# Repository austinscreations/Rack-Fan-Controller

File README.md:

# Rack-Fan-Controller
a controller that can monitor temperature in rack enclosures and control fans

2023-10-25 files have been updated and all JLCPCB PCBa files have now been included.

fan controller is a 4 layer PCB

breakout is 2 layers

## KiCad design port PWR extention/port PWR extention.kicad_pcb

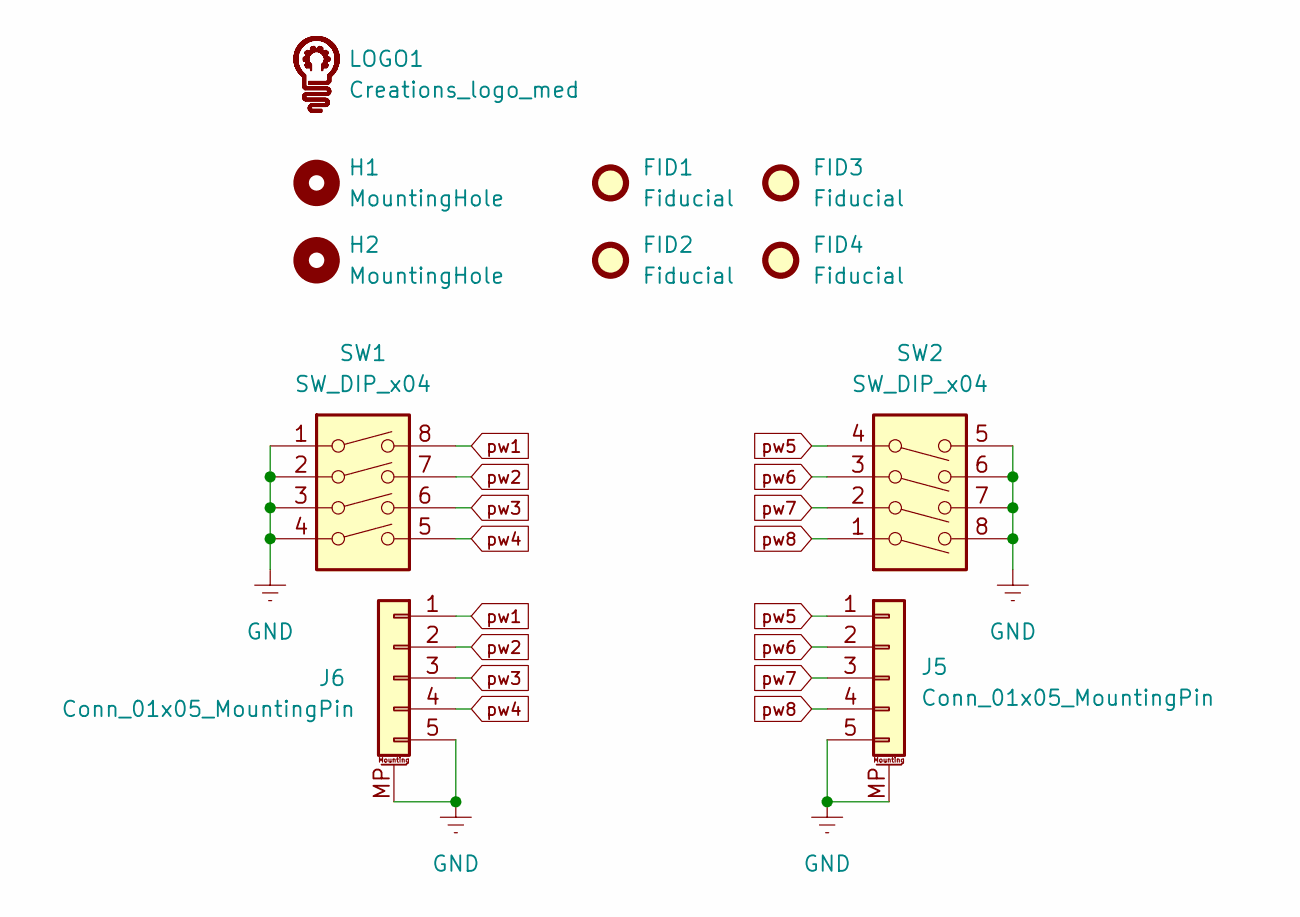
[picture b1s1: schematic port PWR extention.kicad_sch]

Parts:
FID1, FID2, FID3, FID4: Fiducial; Fiducial_1mm_Mask2mm
H1, H2: MountingHole; MountingHole_3.2mm_M3
J5, J6: Conn_01x05_MountingPin; JST_GH_SM05B-GHS-TB_1x05-1MP_P1.25mm_Horizontal; LCSC C225114
LOGO1: Creations_logo_med; Creations logo med
SW1, SW2: SW_DIP_x04; 4P_DIP; LCSC C2758183

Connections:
GNDREF: J5.5, J5.MP (MountPin), J6.5, J6.MP (MountPin), SW1.1, SW1.2, SW1.3, SW1.4, SW2.5, SW2.6, SW2.7, SW2.8
pw1: J6.1, SW1.8
pw2: J6.2, SW1.7
pw3: J6.3, SW1.6
pw4: J6.4, SW1.5
pw5: J5.1, SW2.4
pw6: J5.2, SW2.3
pw7: J5.3, SW2.2
pw8: J5.4, SW2.1

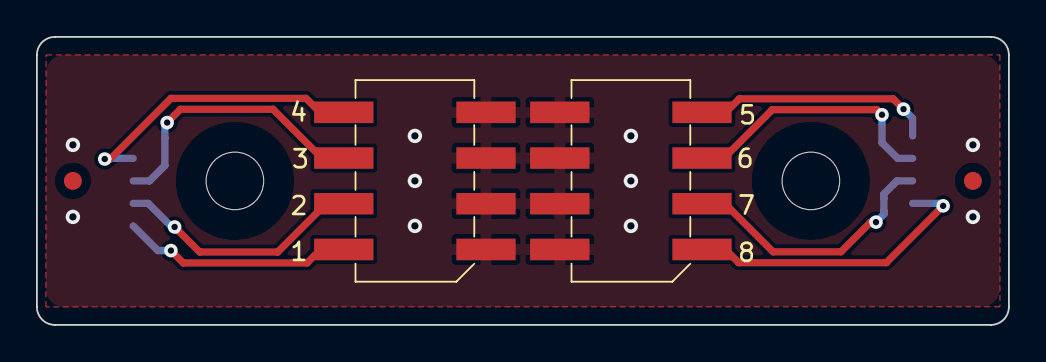
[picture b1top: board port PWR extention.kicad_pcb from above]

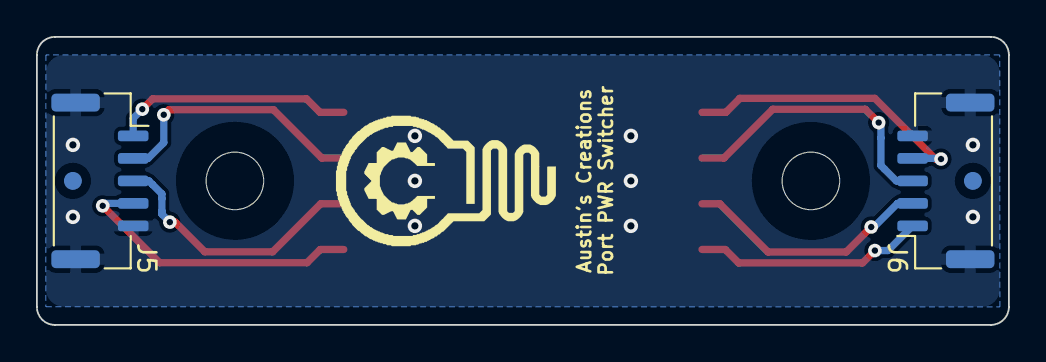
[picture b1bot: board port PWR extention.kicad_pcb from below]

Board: 2 copper layers, 54.0 x 16.0 mm, 11 parts (5 on the bottom side), 9 nets.

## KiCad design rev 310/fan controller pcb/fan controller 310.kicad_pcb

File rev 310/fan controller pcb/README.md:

fan controller has been upgraded to kicad 7 format

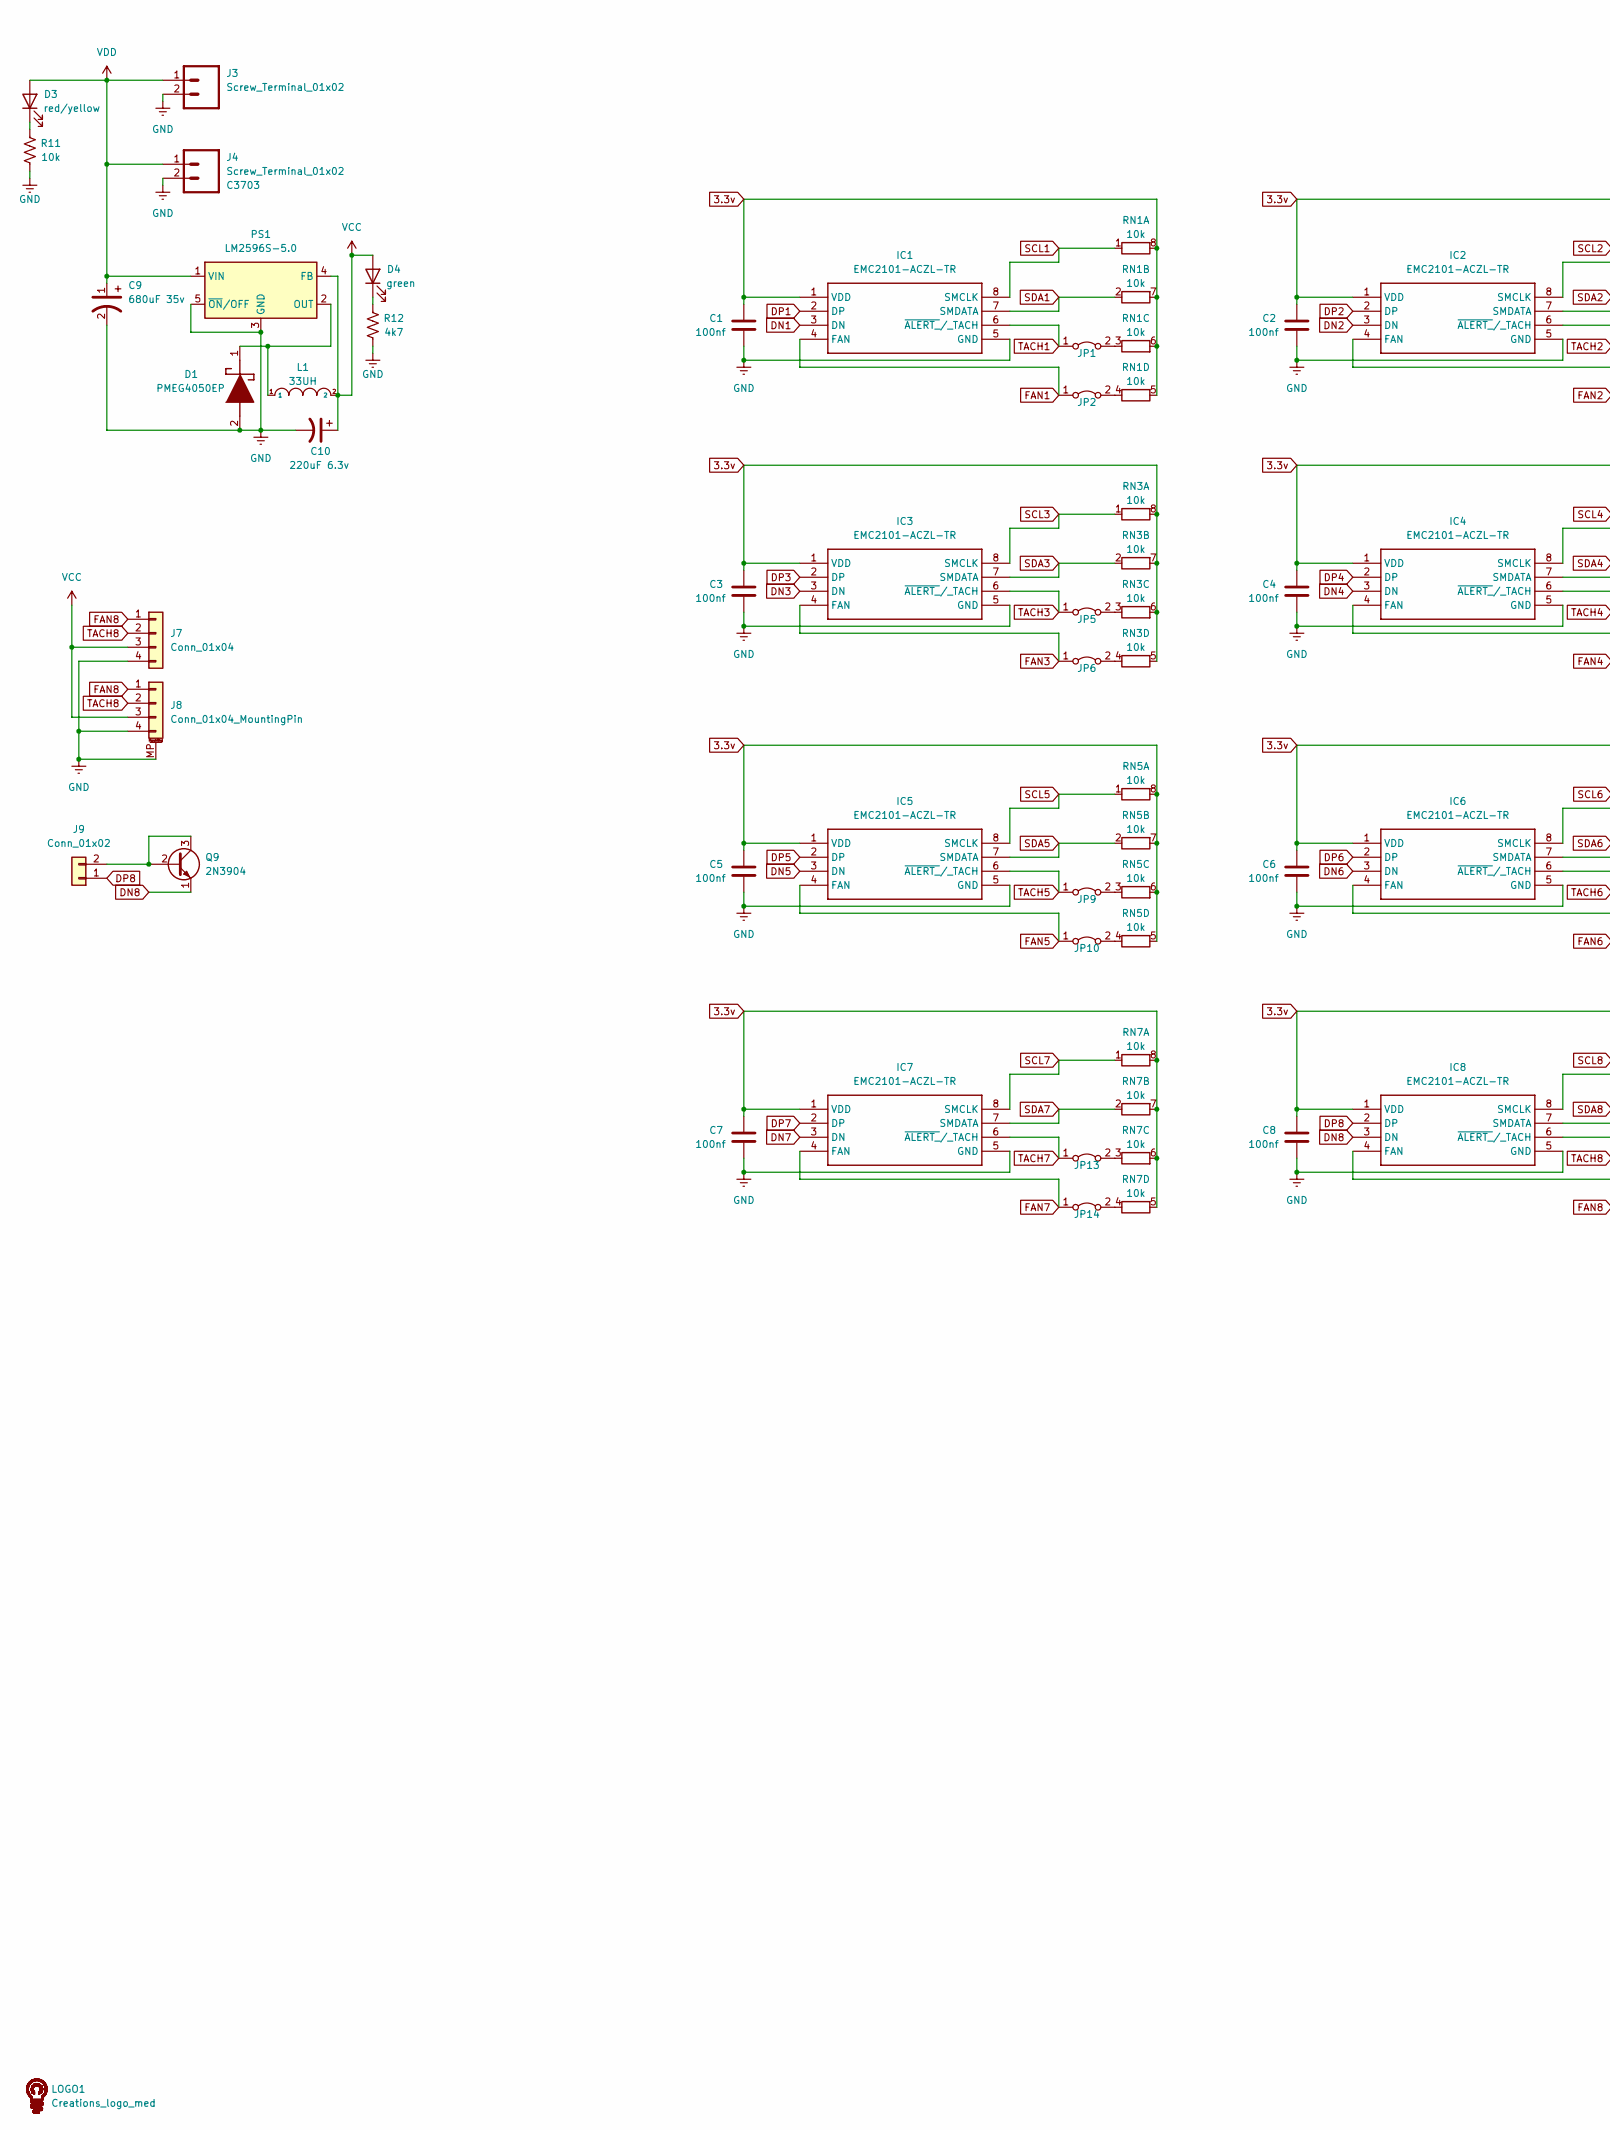
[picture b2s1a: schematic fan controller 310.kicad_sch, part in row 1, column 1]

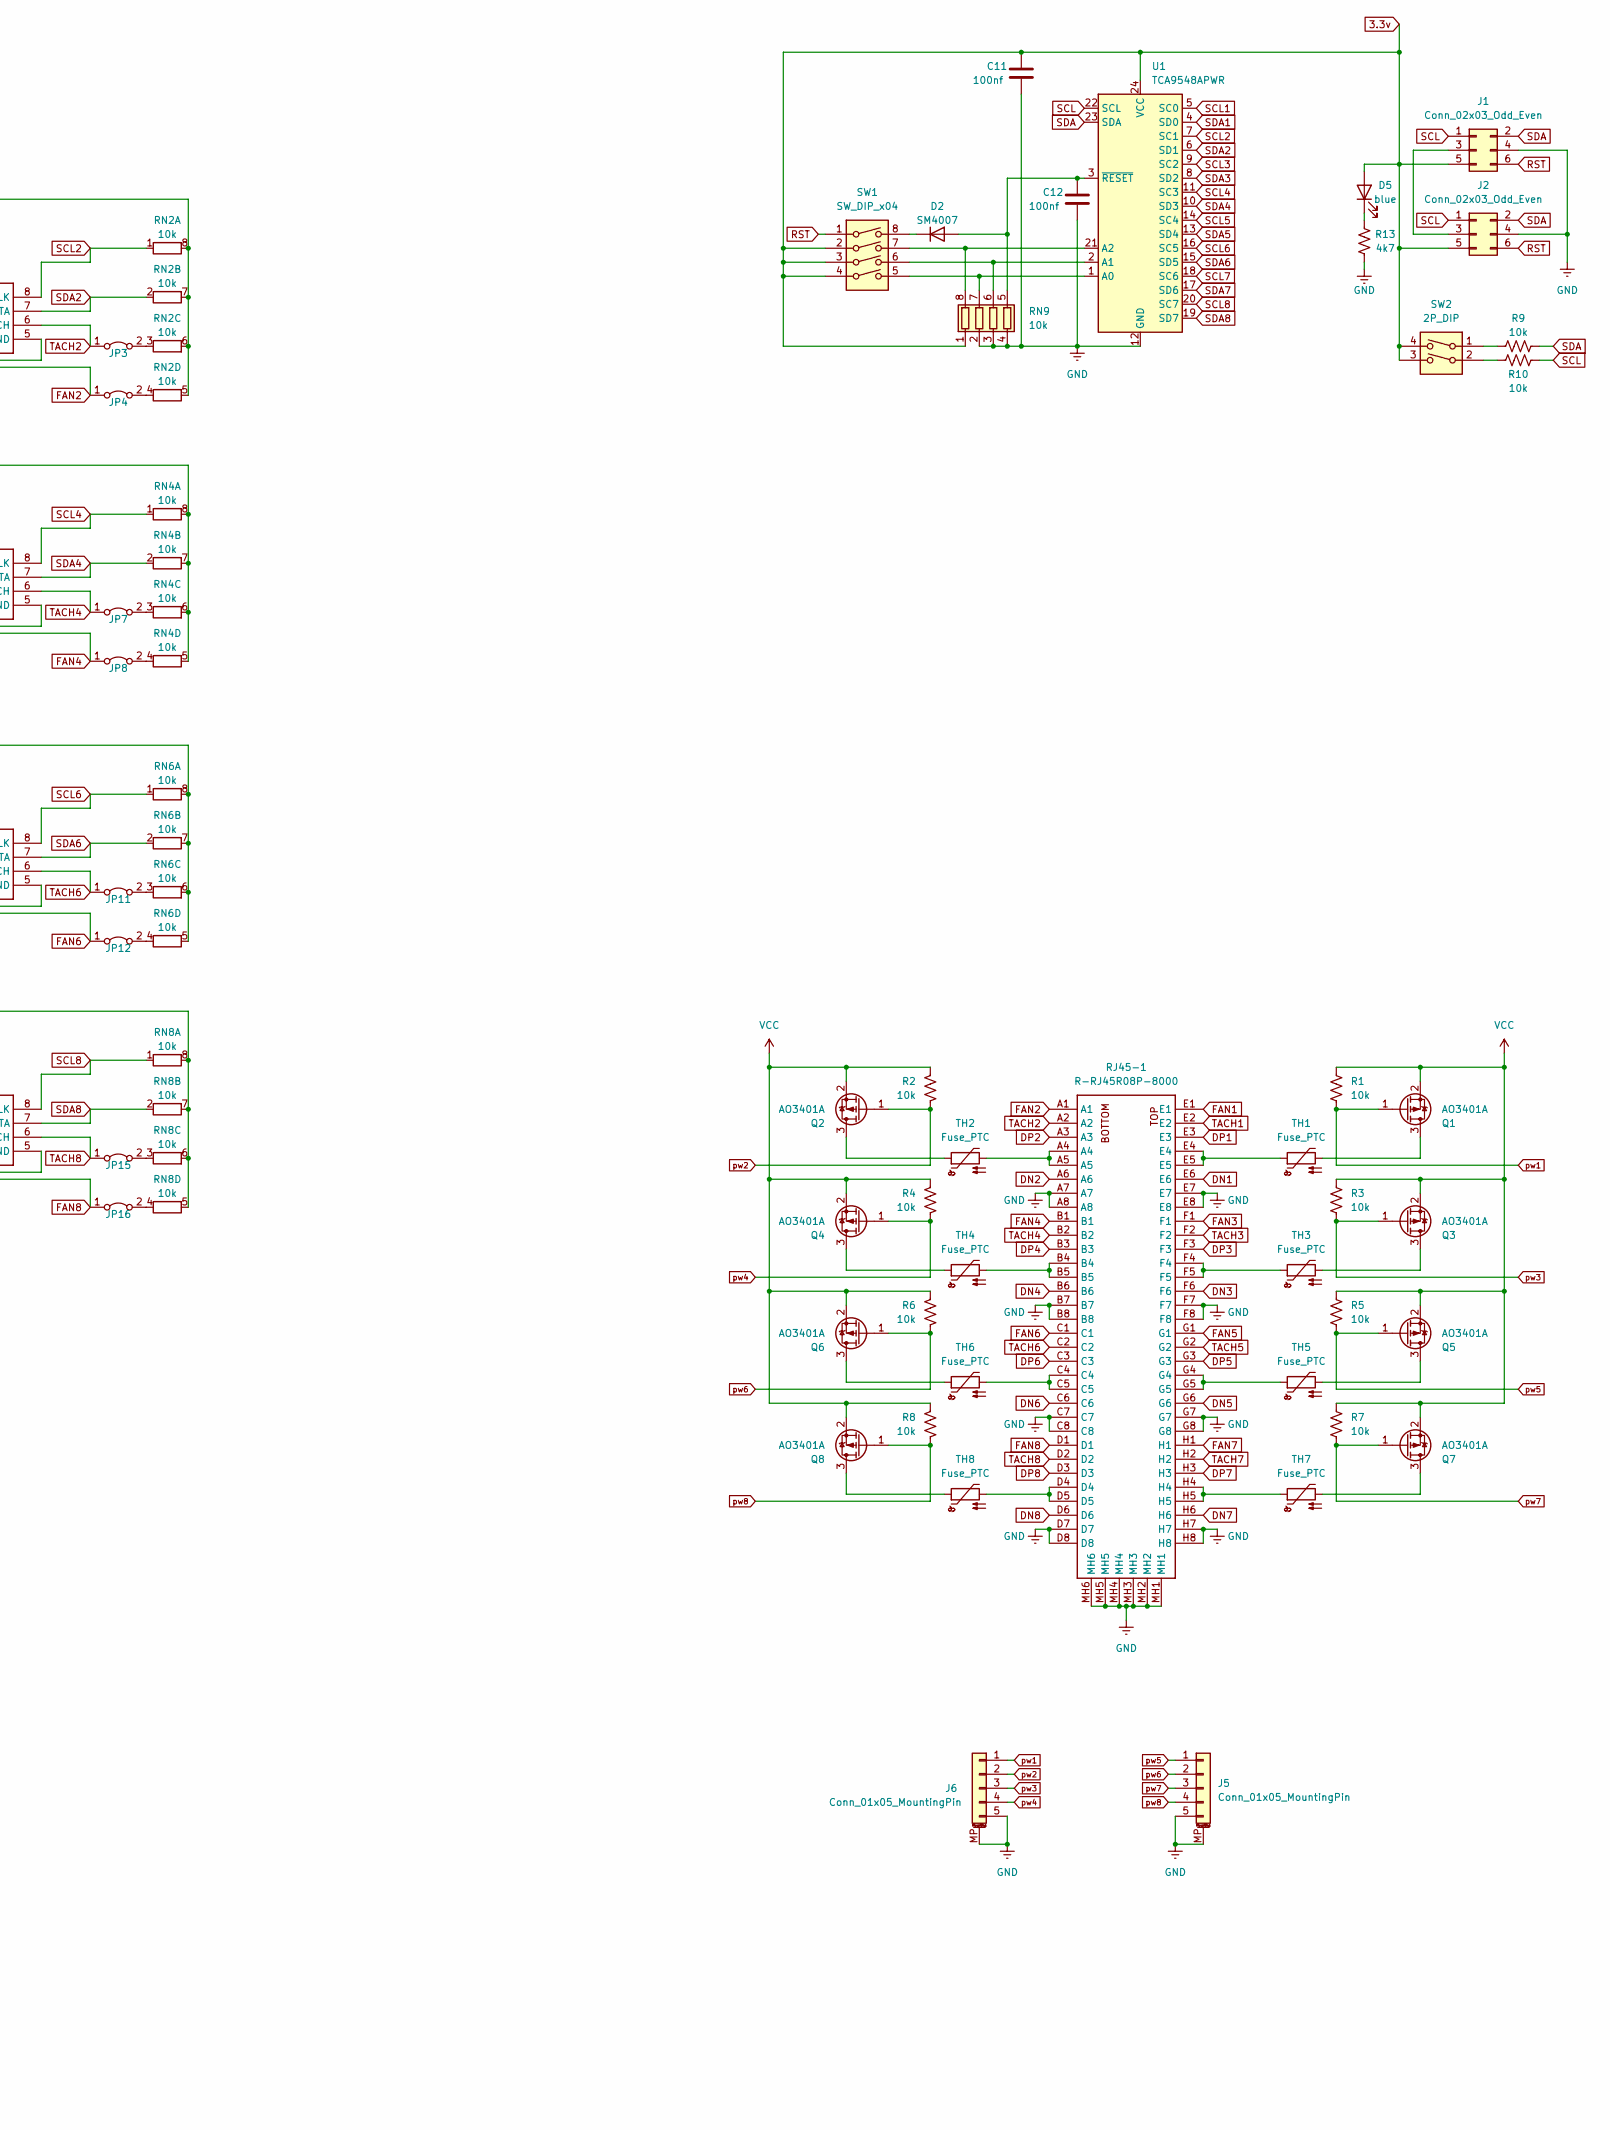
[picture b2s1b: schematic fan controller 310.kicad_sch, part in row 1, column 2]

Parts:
C1, C2, C3, C4, C5, C6, C7, C8, C11, C12: 100nf; C_0603_1608Metric; LCSC C14663
C9: 680uF 35v; large capacitor 12.5d 13.5h; LCSC C98216
C10: 220uF 6.3v; CP_Elec_8x6.2; LCSC C401613
D1: PMEG4050EP; PMEG3050EP; LCSC C96235
D2: SM4007; D_SOD-123F; LCSC C64898
D3: red/yellow; LED_0603_1608Metric; LCSC C72038
D4: green; LED_0603_1608Metric; LCSC C72043
D5: blue; LED_0603_1608Metric; LCSC C72041
IC1, IC2, IC3, IC4, IC5, IC6, IC7, IC8: EMC2101-ACZL-TR; 8-MSOP; LCSC C626967
J1, J2: Conn_02x03_Odd_Even; IDC-Header_2x03_P2.54mm_Vertical; LCSC C132438
J3, J4: Screw_Terminal_01x02; 2pinblock; LCSC C3703
J5, J6: Conn_01x05_MountingPin; JST_GH_SM05B-GHS-TB_1x05-1MP_P1.25mm_Horizontal; LCSC C225114
J7: Conn_01x04; PinHeader_1x04_P2.54mm_Vertical
J8: Conn_01x04_MountingPin; JST_GH_SM04B-GHS-TB_1x04-1MP_P1.25mm_Horizontal; LCSC C225113
J9: Conn_01x02; PinHeader_1x02_P2.54mm_Vertical; LCSC C2829889
JP1, JP2, JP3, JP4, JP5, JP6, JP7, JP8, JP9, JP10, JP11, JP12, JP13, JP14, JP15, JP16: Jumper_2_Bridged; SolderJumper-2_P1.3mm_Bridged_RoundedPad1.0x1.5mm
L1: 33UH; 12x12x8 inductor; LCSC C9400
LOGO1: Creations_logo_med; Creations logo med
PS1: LM2596S-5.0; LM2596S; LCSC C347421
Q1, Q2, Q3, Q4, Q5, Q6, Q7, Q8: AO3401A; SOT-23; LCSC C15127
Q9: 2N3904; TSOT-23; LCSC C18536
R1, R2, R3, R4, R5, R6, R7, R8, R9, R10, R11: 10k; R_0603_1608Metric; LCSC C25804
R12, R13: 4k7; R_0603_1608Metric; LCSC C23162
RJ45-1: R-RJ45R08P-8000; LCSC C386760
RN1, RN2, RN3, RN4, RN5, RN6, RN7, RN8, RN9: 10k; R_Array_Convex_4x0603; LCSC C29718
SW1: SW_DIP_x04; 4P_DIP; LCSC C2758183
SW2: 2P_DIP; LCSC C2758181
TH1, TH2, TH3, TH4, TH5, TH6, TH7, TH8: Fuse_PTC; R_0603_1608Metric; LCSC C883087
U1: TCA9548APWR; TSSOP-24_4.4x7.8mm_P0.65mm; LCSC C130026

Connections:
3.3v: C1.1, C2.1, C3.1, C4.1, C5.1, C6.1, C7.1, C8.1, C11.1, D5.2 (A), IC1.1 (VDD), IC2.1 (VDD), IC3.1 (VDD), IC4.1 (VDD), IC5.1 (VDD), IC6.1 (VDD), IC7.1 (VDD), IC8.1 (VDD), J1.5, J2.5, RN1.5 (R4.2), RN1.6 (R3.2), RN1.7 (R2.2), RN1.8 (R1.2), RN2.5 (R4.2), RN2.6 (R3.2), RN2.7 (R2.2), RN2.8 (R1.2), RN3.5 (R4.2), RN3.6 (R3.2), RN3.7 (R2.2), RN3.8 (R1.2), RN4.5 (R4.2), RN4.6 (R3.2), RN4.7 (R2.2), RN4.8 (R1.2), RN5.5 (R4.2), RN5.6 (R3.2), RN5.7 (R2.2), RN5.8 (R1.2), RN6.5 (R4.2), RN6.6 (R3.2), RN6.7 (R2.2), RN6.8 (R1.2), RN7.5 (R4.2), RN7.6 (R3.2), RN7.7 (R2.2), RN7.8 (R1.2), RN8.5 (R4.2), RN8.6 (R3.2), RN8.7 (R2.2), RN8.8 (R1.2), RN9.1 (R1.1), SW1.2, SW1.3, SW1.4, SW2.3, SW2.4, U1.24 (VCC)
DN1: IC1.3 (DN), RJ45-1.E6
DN2: IC2.3 (DN), RJ45-1.A6
DN3: IC3.3 (DN), RJ45-1.F6
DN4: IC4.3 (DN), RJ45-1.B6
DN5: IC5.3 (DN), RJ45-1.G6
DN6: IC6.3 (DN), RJ45-1.C6
DN7: IC7.3 (DN), RJ45-1.H6
DN8: IC8.3 (DN), Q9.1 (E), RJ45-1.D6
DP1: IC1.2 (DP), RJ45-1.E3
DP2: IC2.2 (DP), RJ45-1.A3
DP3: IC3.2 (DP), RJ45-1.F3
DP4: IC4.2 (DP), RJ45-1.B3
DP5: IC5.2 (DP), RJ45-1.G3
DP6: IC6.2 (DP), RJ45-1.C3
DP7: IC7.2 (DP), RJ45-1.H3
DP8: IC8.2 (DP), J9.1, RJ45-1.D3
FAN1: IC1.4 (FAN), JP2.1 (A), RJ45-1.E1
FAN2: IC2.4 (FAN), JP4.1 (A), RJ45-1.A1
FAN3: IC3.4 (FAN), JP6.1 (A), RJ45-1.F1
FAN4: IC4.4 (FAN), JP8.1 (A), RJ45-1.B1
FAN5: IC5.4 (FAN), JP10.1 (A), RJ45-1.G1
FAN6: IC6.4 (FAN), JP12.1 (A), RJ45-1.C1
FAN7: IC7.4 (FAN), JP14.1 (A), RJ45-1.H1
FAN8: IC8.4 (FAN), J7.1, J8.1, JP16.1 (A), RJ45-1.D1
GNDREF: C1.2, C2.2, C3.2, C4.2, C5.2, C6.2, C7.2, C8.2, C9.2, C10.2, C11.2, C12.2, D1.2 (A), IC1.5 (GND), IC2.5 (GND), IC3.5 (GND), IC4.5 (GND), IC5.5 (GND), IC6.5 (GND), IC7.5 (GND), IC8.5 (GND), J1.4, J2.4, J3.2, J4.2, J5.5, J5.MP (MountPin), J6.5, J6.MP (MountPin), J7.4, J8.4, J8.MP (MountPin), PS1.3 (GND), PS1.5 (~ON/OFF), R11.2, R12.2, R13.2, RJ45-1.A7, RJ45-1.A8, RJ45-1.B7, RJ45-1.B8, RJ45-1.C7, RJ45-1.C8, RJ45-1.D7, RJ45-1.D8, RJ45-1.E7, RJ45-1.E8, RJ45-1.F7, RJ45-1.F8, RJ45-1.G7, RJ45-1.G8, RJ45-1.H7, RJ45-1.H8, RJ45-1.MH1, RJ45-1.MH2, RJ45-1.MH3, RJ45-1.MH4, RJ45-1.MH5, RJ45-1.MH6, RN9.2 (R2.1), RN9.3 (R3.1), RN9.4 (R4.1), U1.12 (GND)
unnamed: D1.1 (K), L1.1, PS1.2 (OUT)
unnamed: C12.1, D2.2 (A), RN9.5 (R4.2), U1.3 (~RESET)
unnamed: D2.1 (K), SW1.8
unnamed: D3.1 (K), R11.1
unnamed: D4.1 (K), R12.1
unnamed: D5.1 (K), R13.1
unnamed: J1.3, J2.3
unnamed: J9.2, Q9.2 (B), Q9.3 (C)
unnamed: JP1.2 (B), RN1.3 (R3.1)
unnamed: JP2.2 (B), RN1.4 (R4.1)
unnamed: JP3.2 (B), RN2.3 (R3.1)
unnamed: JP4.2 (B), RN2.4 (R4.1)
unnamed: JP5.2 (B), RN3.3 (R3.1)
unnamed: JP6.2 (B), RN3.4 (R4.1)
unnamed: JP7.2 (B), RN4.3 (R3.1)
unnamed: JP8.2 (B), RN4.4 (R4.1)
unnamed: JP9.2 (B), RN5.3 (R3.1)
unnamed: JP10.2 (B), RN5.4 (R4.1)
unnamed: JP11.2 (B), RN6.3 (R3.1)
unnamed: JP12.2 (B), RN6.4 (R4.1)
unnamed: JP13.2 (B), RN7.3 (R3.1)
unnamed: JP14.2 (B), RN7.4 (R4.1)
unnamed: JP15.2 (B), RN8.3 (R3.1)
unnamed: JP16.2 (B), RN8.4 (R4.1)
unnamed: Q1.3 (D), TH1.2
unnamed: Q2.3 (D), TH2.1
unnamed: Q3.3 (D), TH3.2
unnamed: Q4.3 (D), TH4.1
unnamed: Q5.3 (D), TH5.2
unnamed: Q6.3 (D), TH6.1
unnamed: Q7.3 (D), TH7.2
unnamed: Q8.3 (D), TH8.1
unnamed: R9.1, SW2.1
unnamed: R10.1, SW2.2
unnamed: RJ45-1.A4, RJ45-1.A5, TH2.2
unnamed: RJ45-1.B4, RJ45-1.B5, TH4.2
unnamed: RJ45-1.C4, RJ45-1.C5, TH6.2
unnamed: RJ45-1.D4, RJ45-1.D5, TH8.2
unnamed: RJ45-1.E4, RJ45-1.E5, TH1.1
unnamed: RJ45-1.F4, RJ45-1.F5, TH3.1
unnamed: RJ45-1.G4, RJ45-1.G5, TH5.1
unnamed: RJ45-1.H4, RJ45-1.H5, TH7.1
unnamed: RN9.8 (R1.2), SW1.7, U1.21 (A2)
unnamed: RN9.7 (R2.2), SW1.5, U1.1 (A0)
unnamed: RN9.6 (R3.2), SW1.6, U1.2 (A1)
RST: J1.6, J2.6, SW1.1
SCL: J1.1, J2.1, R10.2, U1.22 (SCL)
SCL1: IC1.8 (SMCLK), RN1.1 (R1.1), U1.5 (SC0)
SCL2: IC2.8 (SMCLK), RN2.1 (R1.1), U1.7 (SC1)
SCL3: IC3.8 (SMCLK), RN3.1 (R1.1), U1.9 (SC2)
SCL4: IC4.8 (SMCLK), RN4.1 (R1.1), U1.11 (SC3)
SCL5: IC5.8 (SMCLK), RN5.1 (R1.1), U1.14 (SC4)
SCL6: IC6.8 (SMCLK), RN6.1 (R1.1), U1.16 (SC5)
SCL7: IC7.8 (SMCLK), RN7.1 (R1.1), U1.18 (SC6)
SCL8: IC8.8 (SMCLK), RN8.1 (R1.1), U1.20 (SC7)
SDA: J1.2, J2.2, R9.2, U1.23 (SDA)
SDA1: IC1.7 (SMDATA), RN1.2 (R2.1), U1.4 (SD0)
SDA2: IC2.7 (SMDATA), RN2.2 (R2.1), U1.6 (SD1)
SDA3: IC3.7 (SMDATA), RN3.2 (R2.1), U1.8 (SD2)
SDA4: IC4.7 (SMDATA), RN4.2 (R2.1), U1.10 (SD3)
SDA5: IC5.7 (SMDATA), RN5.2 (R2.1), U1.13 (SD4)
SDA6: IC6.7 (SMDATA), RN6.2 (R2.1), U1.15 (SD5)
SDA7: IC7.7 (SMDATA), RN7.2 (R2.1), U1.17 (SD6)
SDA8: IC8.7 (SMDATA), RN8.2 (R2.1), U1.19 (SD7)
TACH1: IC1.6 (~ALERT_/_TACH), JP1.1 (A), RJ45-1.E2
TACH2: IC2.6 (~ALERT_/_TACH), JP3.1 (A), RJ45-1.A2
TACH3: IC3.6 (~ALERT_/_TACH), JP5.1 (A), RJ45-1.F2
TACH4: IC4.6 (~ALERT_/_TACH), JP7.1 (A), RJ45-1.B2
TACH5: IC5.6 (~ALERT_/_TACH), JP9.1 (A), RJ45-1.G2
TACH6: IC6.6 (~ALERT_/_TACH), JP11.1 (A), RJ45-1.C2
TACH7: IC7.6 (~ALERT_/_TACH), JP13.1 (A), RJ45-1.H2
TACH8: IC8.6 (~ALERT_/_TACH), J7.2, J8.2, JP15.1 (A), RJ45-1.D2
VCC: C10.1, D4.2 (A), J7.3, J8.3, L1.2, PS1.4 (FB), Q1.2 (S), Q2.2 (S), Q3.2 (S), Q4.2 (S), Q5.2 (S), Q6.2 (S), Q7.2 (S), Q8.2 (S), R1.1, R2.2, R3.1, R4.2, R5.1, R6.2, R7.1, R8.2
VDD: C9.1, D3.2 (A), J3.1, J4.1, PS1.1 (VIN)
pw1: J6.1, Q1.1 (G), R1.2
pw2: J6.2, Q2.1 (G), R2.1
pw3: J6.3, Q3.1 (G), R3.2
pw4: J6.4, Q4.1 (G), R4.1
pw5: J5.1, Q5.1 (G), R5.2
pw6: J5.2, Q6.1 (G), R6.1
pw7: J5.3, Q7.1 (G), R7.2
pw8: J5.4, Q8.1 (G), R8.1

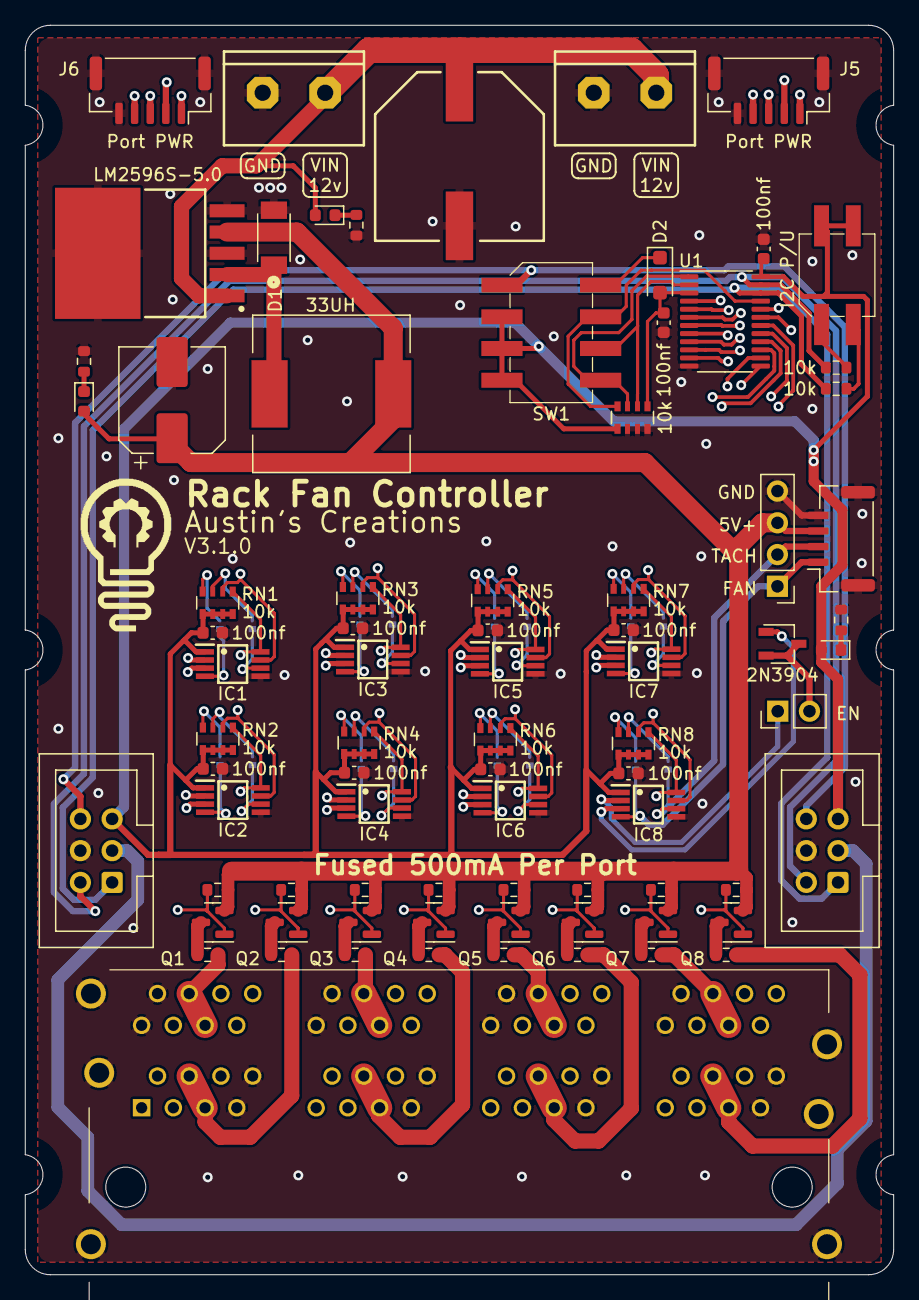
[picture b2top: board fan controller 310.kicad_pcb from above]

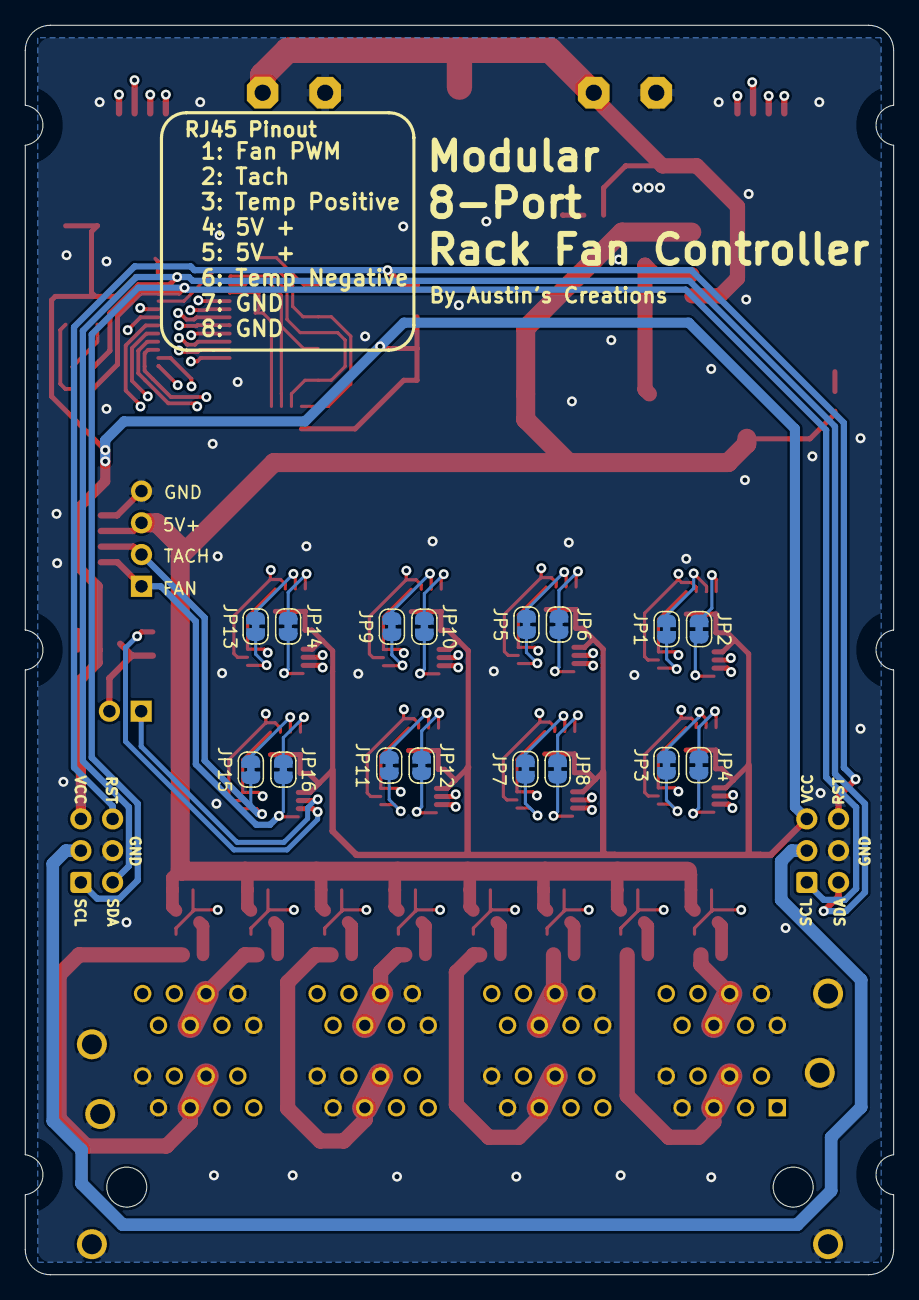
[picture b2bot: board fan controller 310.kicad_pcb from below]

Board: 4 copper layers, 69.5 x 100.0 mm, 96 parts (16 on the bottom side), 108 nets.

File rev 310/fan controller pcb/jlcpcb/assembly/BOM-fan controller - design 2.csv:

Comment,Designator,Footprint,LCSC
TCA9548APWR,U1,TSSOP-24_4.4x7.8mm_P0.65mm,C130026
Conn_02x03_Odd_Even,"J1,J2",IDC-Header_2x03_P2.54mm_Vertical,C132438
100nf,"C1,C11,C12,C2,C3,C4,C5,C6,C7,C8",C_0603_1608Metric,C14663
AO3401A,"Q1,Q2,Q3,Q4,Q5,Q6,Q7,Q8",SOT-23,C15127
2N3904,Q9,TSOT-23,C18536
Conn_01x04_MountingPin,J8,JST_GH_SM04B-GHS-TB_1x04-1MP_P1.25mm_Horizontal,C225113
Conn_01x05_MountingPin,"J5,J6",JST_GH_SM05B-GHS-TB_1x05-1MP_P1.25mm_Horizontal,C225114
4k7,"R12,R13",R_0603_1608Metric,C23162
10k,"R1,R10,R11,R2,R3,R4,R5,R6,R7,R8,R9",R_0603_1608Metric,C25804
2P_DIP,SW2,2P_DIP,C2758181
SW_DIP_x04,SW1,4P_DIP,C2758183
Conn_01x02,J9,PinHeader_1x02_P2.54mm_Vertical,C2829889
10k,"RN1,RN2,RN3,RN4,RN5,RN6,RN7,RN8,RN9",R_Array_Convex_4x0603,C29718
LM2596S-5.0,PS1,LM2596S,C347421
Screw_Terminal_01x02,"J3,J4",2pinblock,C3703
R-RJ45R08P-8000,RJ45-1,R-RJ45R08P-8000,C386760
220uF 6.3v,C10,CP_Elec_8x6.2,C401613
EMC2101-ACZL-TR,"IC1,IC2,IC3,IC4,IC5,IC6,IC7,IC8",8-MSOP,C626967
SM4007,D2,D_SOD-123F,C64898
red/yellow,D3,LED_0603_1608Metric,C72038
blue,D5,LED_0603_1608Metric,C72041
green,D4,LED_0603_1608Metric,C72043
Fuse_PTC,"TH1,TH2,TH3,TH4,TH5,TH6,TH7,TH8",R_0603_1608Metric,C883087
33UH,L1,12x12x8 inductor,C9400
PMEG4050EP,D1,PMEG3050EP,C96235
680uF 35v,C9,large capacitor 12.5d 13.5h,C98216
Conn_01x04,J7,PinHeader_1x04_P2.54mm_Vertical,

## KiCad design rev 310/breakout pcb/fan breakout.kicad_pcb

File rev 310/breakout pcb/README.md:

fan breakout has been upgraded to kicad 7 format

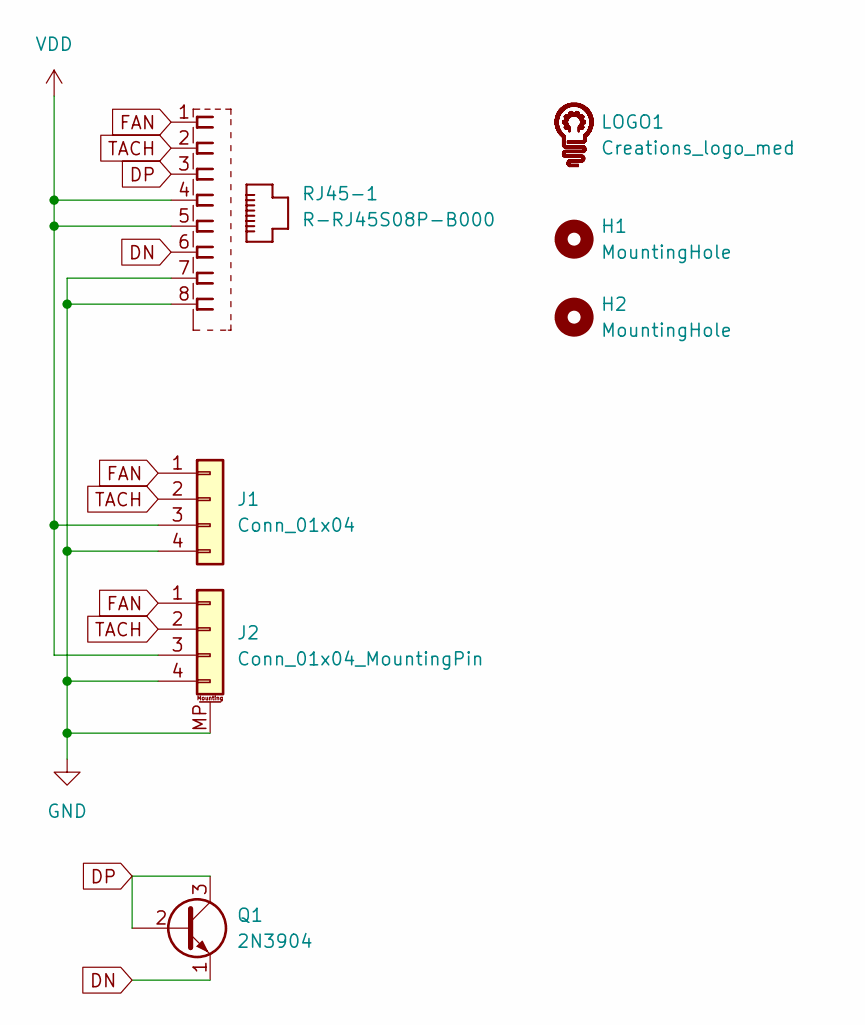
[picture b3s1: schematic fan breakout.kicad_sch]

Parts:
H1, H2: MountingHole; MountingHole_3.2mm_M3
J1: Conn_01x04; PinHeader_1x04_P2.54mm_Vertical
J2: Conn_01x04_MountingPin; JST_GH_SM04B-GHS-TB_1x04-1MP_P1.25mm_Horizontal; LCSC C225113
LOGO1: Creations_logo_med; Creations logo med
Q1: 2N3904; TSOT-23; LCSC C18536
RJ45-1: R-RJ45S08P-B000; LCSC C386763

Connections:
DN: Q1.1 (E), RJ45-1.6
DP: Q1.2 (B), Q1.3 (C), RJ45-1.3
FAN: J1.1, J2.1, RJ45-1.1
GND: J1.4, J2.4, J2.MP (MountPin), RJ45-1.7, RJ45-1.8
TACH: J1.2, J2.2, RJ45-1.2
VDD: J1.3, J2.3, RJ45-1.4, RJ45-1.5

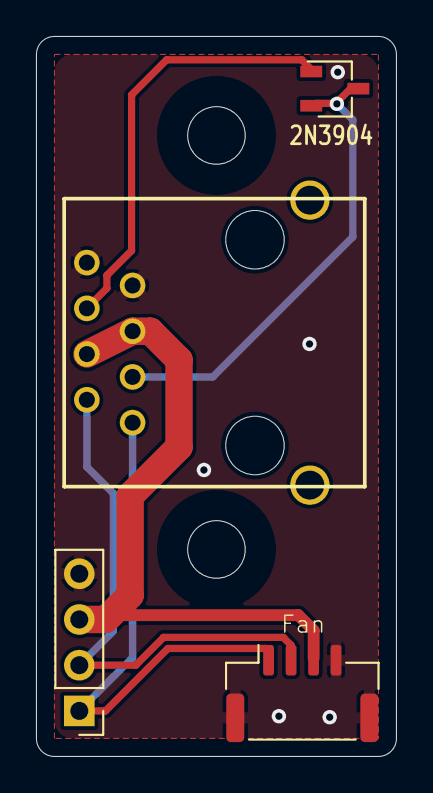
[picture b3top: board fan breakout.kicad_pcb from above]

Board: 2 copper layers, 20.0 x 40.0 mm, 7 parts (1 on the bottom side), 6 nets.

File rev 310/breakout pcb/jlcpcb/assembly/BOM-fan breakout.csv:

Comment,Designator,Footprint,LCSC
2N3904,Q1,TSOT-23,C18536
Conn_01x04_MountingPin,J2,JST_GH_SM04B-GHS-TB_1x04-1MP_P1.25mm_Horizontal,C225113
R-RJ45S08P-B000,RJ45-1,R-RJ45S08P-B000,C386763
MountingHole,H2,MountingHole_3.2mm_M3,
MountingHole,H1,MountingHole_3.2mm_M3,
Conn_01x04,J1,PinHeader_1x04_P2.54mm_Vertical,
Creations_logo_med,LOGO1,Creations logo med,

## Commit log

2023-05-07 add warning
